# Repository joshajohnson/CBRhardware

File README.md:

# Canberra Hardware Meetup
A monthly hardware meetup for anyone interested in electronics / hardware. 

Held on the second Monday of each month, 6-8pm, at [Infosect](https://www.infosectcbr.com.au), 2/9 Beaconsfield Street, Fyshwick, 2609 ACT.  

We'll cover topics such as PCB design / layout, embedded programming, tips and tricks to make hardware less hard, and everything in between.   

All skill levels welcome, and feel free to bring along any projects you are working on or need a hand with as well.  

If you have any suggestions about topics to discuss / changes to make, please get in touch.

## 11/11/19 - Test and Measurement
An unprepared talk on the wonderful world which is electronic test and measurement, discussing common tools, how they work, pitfalls, where to cheap out, and Josh's unsuccessful attempt at designing a VNA.

### Future Events 

|Date|Topic|
|-|-|
|11/11/19|Test and Measurement|

### Past Events

|Date|Topic|
|-|-|
|8/4/19|Intro to KiCad / How to design a PCB|
|13/5/19|uC101: Intro to Microcontrollers / How to interface to the real world|
|10/6/19|Breadboard to PC Board|
|8/7/19|uC102: Embedded Communication Protocols / ADC|
|12/8/19|Further PCB Design / Manufacturing / KiCad|
|9/9/19|WTFpga Workshop|
|28/10/19|More FPGA!|

## 8/4/19 - Intro to KiCad / How to design a PCB

A workshop going over how to design a printed circuit board in KiCad.  

Aimed at beginners who haven't designed many boards before, or folks who have design experience but haven't used KiCad much.  

Feel free to bring a laptop with [KiCad 5.1](http://kicad-pcb.org/download/) installed if you want to design along, otherwise just come along and ask questions as we go. I would highly suggest bringing a mouse as well, as layout with a trackpad is not much fun. 

The [SAO101](/SAO101) folder contains resources which will be used on the night.

## 13/5/19 - uC101: Intro to Microcontrollers / How to interface with the real world

A workshop delving into the low level details of how you can use a microcontroller to interface with the physical world.   

Will be going below the Arduino abstraction layer to directly interface with registers and peripherals on an ATmega328p, allowing us to interact with switches, rotary encoders, and LEDs.   

You'll learn why buttons don't turn on just once when you press them and ways to get around this issue, along with how custom silicon on the chip can take the workload off your processor. 

If time allows will also cover communication protocols and ADCs, however that will most likely be a different months topic. 

Please bring along a laptop with the [Arduino IDE](https://www.arduino.cc/en/main/software) installed, along with a Mini-USB cable to connect to the microcontroller with. 
Josh will have the installer files and spare USB cables on the night, but will not be enough for everyone. 
The [uC101](/uC101) folder contains resources which will be used.

## 10/6/19 - Breadboard to PC Board

Prototyped a circuit on a breadboard, and want to get it onto a printed cicruit board but not sure how? If so this talk is for you!  
We will be going over how to to take a bunch of breakout boards with wires flying between them and get it onto a professional looking PCB.  
Multiple common microcontrollers, breakout boards, and other handy components will be covered, allowing you to take your electronic design to the next level. 

## 8/7/19 - uC102: Embedded Communication Protocols / ADC

Following on from uC101 in which the low level functions of a microcontroller were explored, this workshop will delve into how embedded devices communicate, along with touching on Analog to Digital Converters. 

UART, SPI, I2C, and JTAG will all be discussed, along with writing code and communicating with UART, SPI, and I2C devices.

Please bring along a laptop with the [Arduino IDE](https://www.arduino.cc/en/main/software) installed. 
Josh will have the installer files on the night as well. 
The [uC102](/uC102) folder contains resources which will be used.

## 12/7 8/19 - furtherPCB: PCB Design / Manufacturing / KiCad

A workshop delving into more detail about PCB design, including 4+ layer stack ups, impedance controlled traces and boards, layout tips, and looking at what the modern state of the art is in PCB manufacturing and assembly.

We will also discuss tools and how to use them to achieve the above mentioned design considerations, followed by looking at some of Josh's projects and identifying where these techniques have been utilised.

## 9/9/19 - WTFpga Workshop

2 hour crash course in FPGAs and Verilog.

Unlike most meetups where all you need to do is show up, this workshop will require software to be installed in advance and hardware to be acquired.

Have a read of the [WTFpga Readme](WTFpga/README.md) and let Josh know if there are any questions.

## 28/10/19 Topic: FPGA Workshop, continued. 
Following on from the WTFpga workshop, we will discuss some of the key details about FPGA function, programming, debugging, and hopefully explain some of the questions which arose at the previous workshop.

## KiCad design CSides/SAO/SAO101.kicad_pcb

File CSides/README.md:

# Electronic Hardware Design

This talk will cover the process of designing, manufacturing, and assembling electronic hardware, with a focus on how to use KiCad to design and layout a PCB. 
Using a keyboard Josh designed as an example, aspects of the process such as circuit design, PCB layout and assembly, along with programming and mechanical design will be demonstrated, with the goal of providing an overview of the process for anyone interested in designing their own hardware.

**Josh Johnson**

Josh is passionate about electronic design and spends far too much time designing boards and writing firmware. 
He is currently in his final semester of university, and is looking forward to joining the real world next year with a product development role in automotive. 

### Keyboard Design Files
Design files for the keyboard discussed can be found [here](https://github.com/joshajohnson/MacroKeyboard).  
If you are considering assembling the above board, modifying it for your own use, or designing one from scratch, feel free to get in touch as there are some things I would change on that board for a new revision. 

### SAO Design
The `SAO` folder has a partial KiCad project with everything you need to make a SAO for BSides 2020.
The schematic is known good, so all you need to do is make an awesome design and ensure is passes DRC.
A completed design is [also available](https://github.com/joshajohnson/CBRhardware/tree/master/SAO101), along with Josh's 2019 [WarGames SAO](https://github.com/joshajohnson/WarGames_SAO).
### Questions? 
Feel free to get in touch with any questions.  
No guarantees I'll be able to help, but will try my best! 

Email: `josh at joshajohnson dot com`  
Twitter: `@_joshajohnson`  
BSidesCbr Slack: `josh`

### Resources:   
[PCB Design in Reverse](https://www.youtube.com/watch?v=CV68US8gZMk)  
[PCB Design Tutorial PDF](https://alternatezone.com/electronics/files/PCBDesignTutorialRevA.pdf)  
[Chris Gammell / Contextual Electronics](https://www.youtube.com/user/contextualelectronic/videos)  
[Digikey KiCad Series](https://www.youtube.com/watch?v=vaCVh2SAZY4)  
[Lintek Process Capabilities](http://www.lintek.com.au/wordpress/wp-content/uploads/Design-Capabilities-v2.7.pdf)
[Robert Feranec - Layout Videos](https://www.youtube.com/user/matarofe/videos)  
[100 Hardware Design Tips](https://www.youtube.com/watch?v=ZpMvKJzZk90&list=PLXvLToQzgzddPKq_txEXNe0pxaSHqPtMO)    
[Review of PCB Layout](https://www.youtube.com/watch?v=HZVod5AFrVI)  
[PCB Art](http://www.andrewsowa.com/blog/2017/3/19/creating-the-benchoff-nickel)  
[How I make Shitty Add-ons](https://www.youtube.com/watch?v=61NFK9KW_4s)  
[Interactive BOM](https://github.com/openscopeproject/InteractiveHtmlBom)

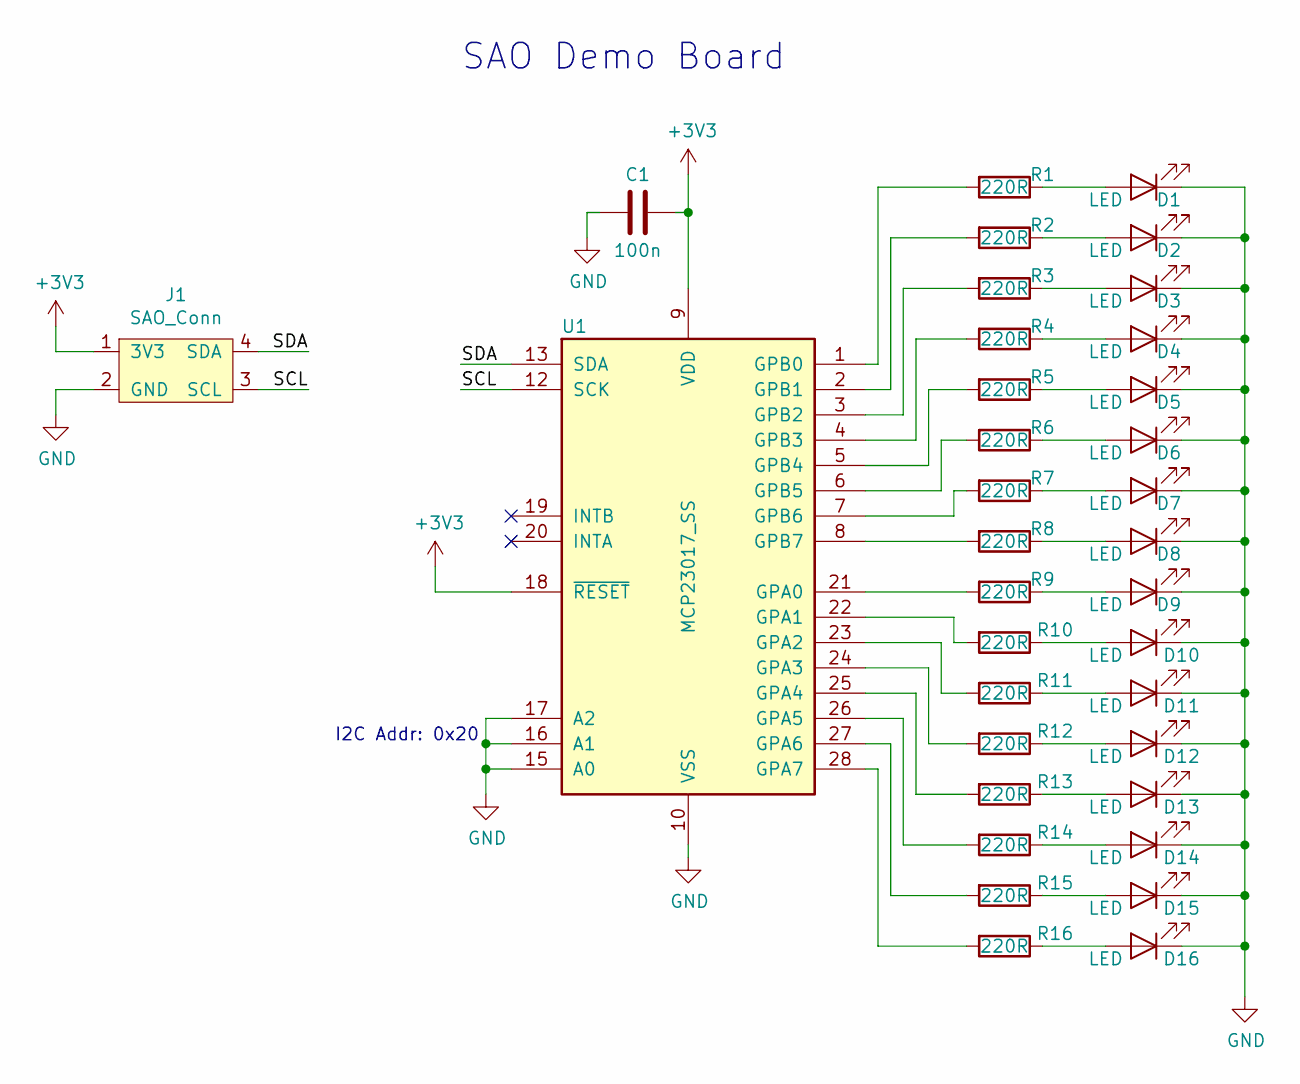
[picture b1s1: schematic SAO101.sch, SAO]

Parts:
C1: 100n; C_0805_2012Metric
D1, D2, D3, D4, D5, D6, D7, D8, D9, D10, D11, D12, D13, D14, D15, D16: LED; LED_1206_3216Metric_Pad1.42x1.75mm_HandSolder
J1: SAO_Conn; SAO
R1, R2, R3, R4, R5, R6, R7, R8, R9, R10, R11, R12, R13, R14, R15, R16: 220R; R_1206_3216Metric_Pad1.42x1.75mm_HandSolder
U1: MCP23017_SS; SSOP-28_5.3x10.2mm_P0.65mm

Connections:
+3V3: C1.1, J1.1 (3V3), U1.9 (VDD), U1.18 (~RESET~)
/SCL: J1.3 (SCL), U1.12 (SCK)
/SDA: J1.4 (SDA), U1.13 (SDA)
GND: C1.2, D1.1 (K), D2.1 (K), D3.1 (K), D4.1 (K), D5.1 (K), D6.1 (K), D7.1 (K), D8.1 (K), D9.1 (K), D10.1 (K), D11.1 (K), D12.1 (K), D13.1 (K), D14.1 (K), D15.1 (K), D16.1 (K), J1.2 (GND), U1.10 (VSS), U1.15 (A0), U1.16 (A1), U1.17 (A2)
unnamed: D1.2 (A), R1.1
unnamed: D2.2 (A), R2.1
unnamed: D3.2 (A), R3.1
unnamed: D4.2 (A), R4.1
unnamed: D5.2 (A), R5.1
unnamed: D6.2 (A), R6.1
unnamed: D7.2 (A), R7.1
unnamed: D8.2 (A), R8.1
unnamed: D9.2 (A), R9.1
unnamed: D10.2 (A), R10.1
unnamed: D11.2 (A), R11.1
unnamed: D12.2 (A), R12.1
unnamed: D13.2 (A), R13.1
unnamed: D14.2 (A), R14.1
unnamed: D15.2 (A), R15.1
unnamed: D16.2 (A), R16.1
unnamed: R1.2, U1.1 (GPB0)
unnamed: R2.2, U1.2 (GPB1)
unnamed: R3.2, U1.3 (GPB2)
unnamed: R4.2, U1.4 (GPB3)
unnamed: R5.2, U1.5 (GPB4)
unnamed: R6.2, U1.6 (GPB5)
unnamed: R7.2, U1.7 (GPB6)
unnamed: R8.2, U1.8 (GPB7)
unnamed: R9.2, U1.21 (GPA0)
unnamed: R10.2, U1.22 (GPA1)
unnamed: R11.2, U1.23 (GPA2)
unnamed: R12.2, U1.24 (GPA3)
unnamed: R13.2, U1.25 (GPA4)
unnamed: R14.2, U1.26 (GPA5)
unnamed: R15.2, U1.27 (GPA6)
unnamed: R16.2, U1.28 (GPA7)

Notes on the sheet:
SAO Demo Board
I2C Addr: 0x20

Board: 2 copper layers, 35 parts (0 on the bottom side), 36 nets, no tracks yet.

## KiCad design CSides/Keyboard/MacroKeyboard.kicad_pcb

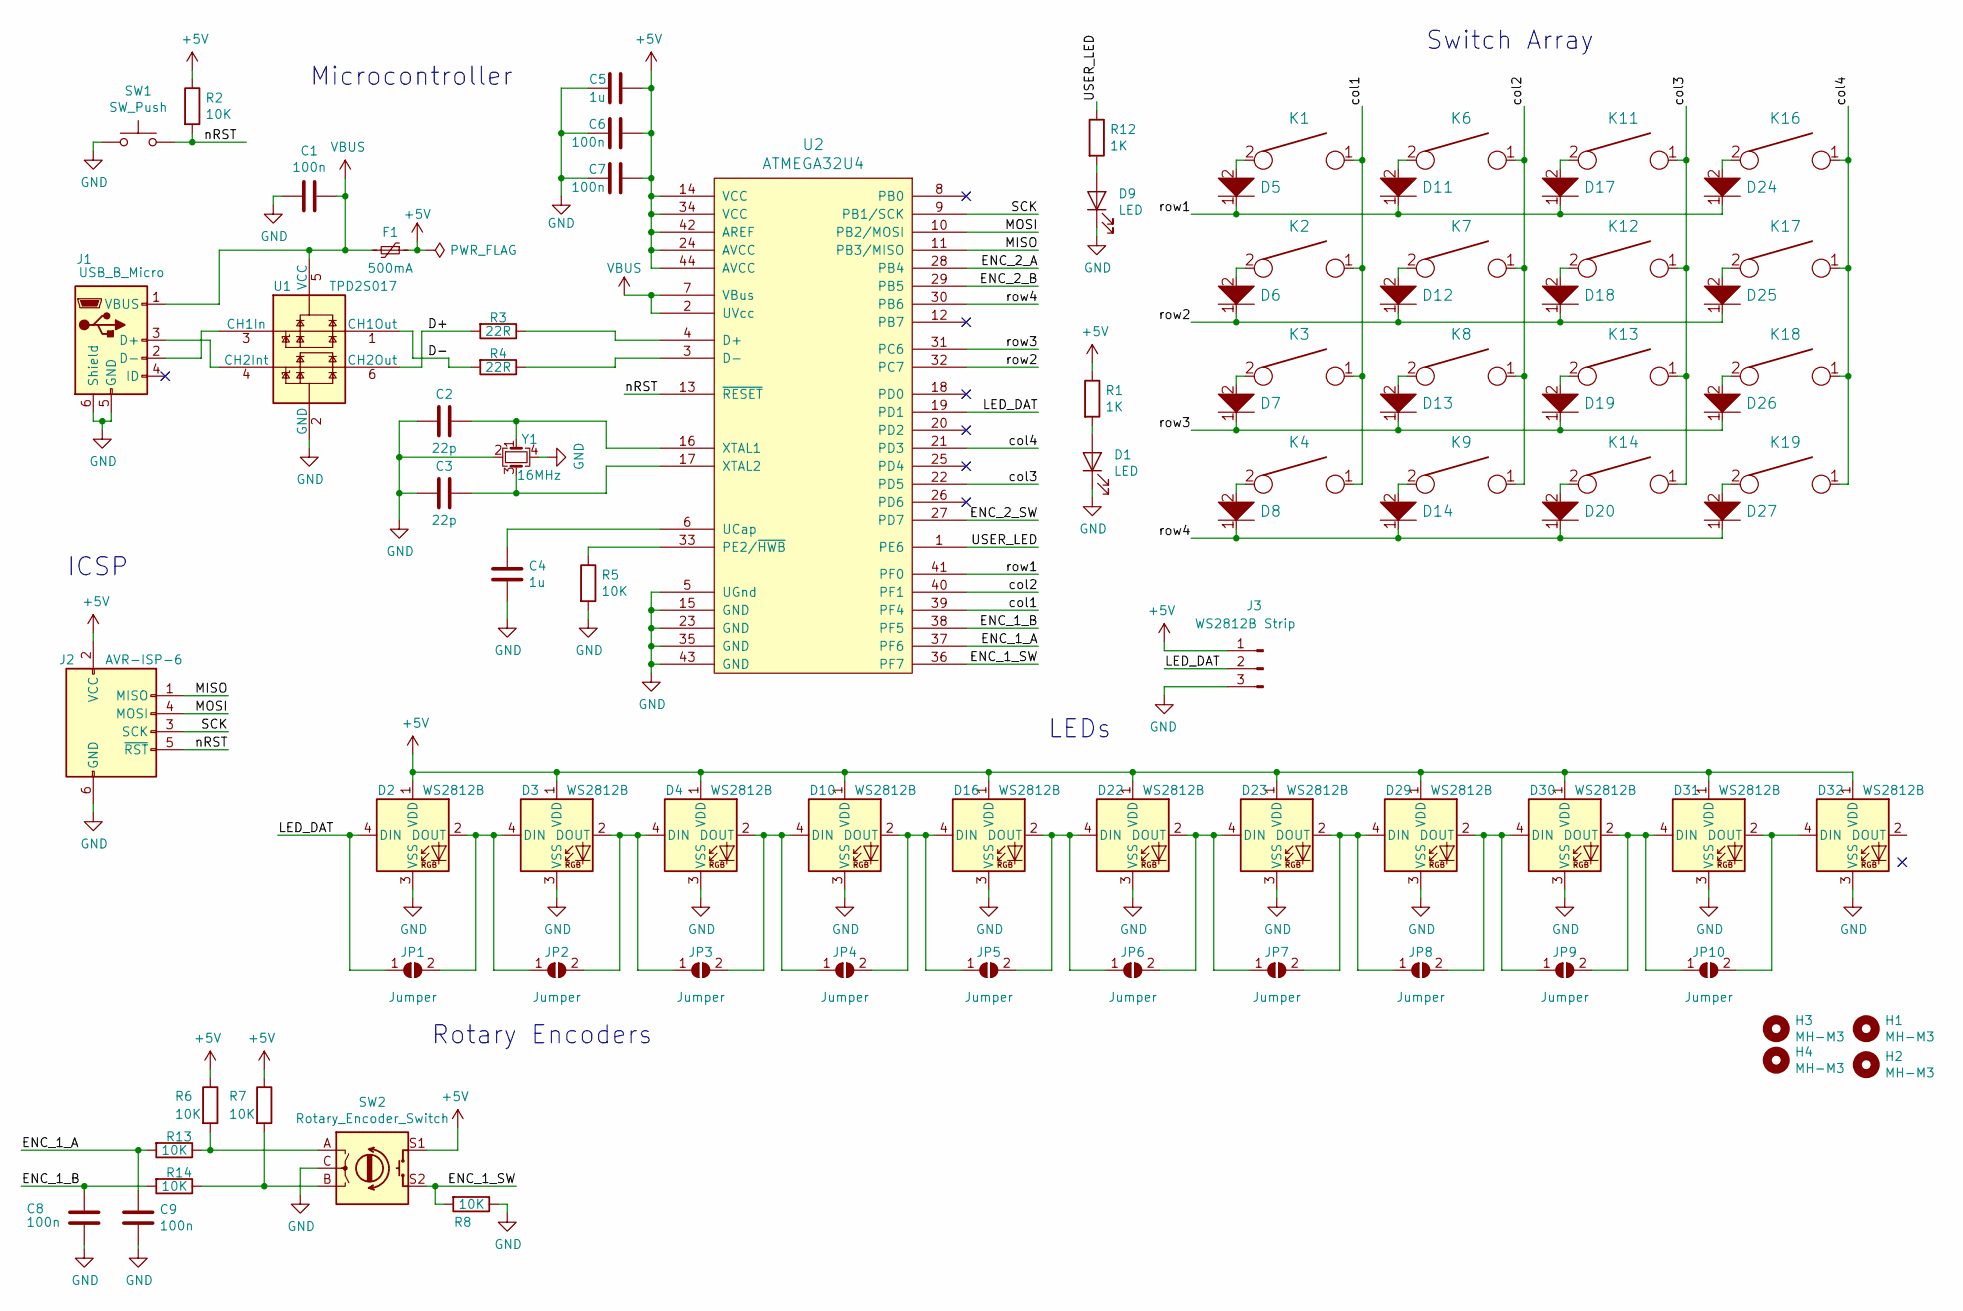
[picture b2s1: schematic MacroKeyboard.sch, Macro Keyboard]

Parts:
C1, C6, C7, C8, C9: 100n; C_0603_1608Metric
C2, C3: 22p; C_0603_1608Metric
C4, C5: 1u; C_0603_1608Metric
D1, D9: LED; LED_0603_1608Metric
D2, D3, D4, D10, D16, D22, D23, D29, D30, D31, D32: WS2812B; LED_WS2812B_PLCC4_5.0x5.0mm_P3.2mm
D5, D6, D7, D8, D11, D12, D13, D14, D17, D18, D19, D20, D24, D25, D26, D27: D; D_SOD-323
F1: 500mA; Fuse_0805_2012Metric
H1, H2, H3, H4: MH-M3; MountingHole_3.2mm_M3_ISO14580
J1: USB_B_Micro; MicroUSB_Aliexpress
J2: AVR-ISP-6; AVR_Programmer_SMD
J3: WS2812B Strip; PinPad_1x03_P2.54mm
JP1, JP2, JP3, JP4, JP5, JP6, JP7, JP8, JP9, JP10: Jumper; SolderJumper-2_P1.3mm_Open_RoundedPad1.0x1.5mm
K1, K2, K3, K4, K6, K7, K8, K9, K11, K12, K13, K14, K16, K17, K18, K19: KEYSW; SW_Cherry_MX1A_1.00u_PCB
R1, R12: 1K; R_0603_1608Metric
R2, R5, R6, R7, R8, R13, R14: 10K; R_0603_1608Metric
R3, R4: 22R; R_0603_1608Metric
SW1: SW_Push; Small_Tact_Switch
SW2: Rotary_Encoder_Switch; RotaryEncoder_Alps_EC11E-Switch_Vertical_H20mm_CircularMoun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
U1: TPD2S017; SOT-23-6
U2: ATMEGA32U4; TQFP-44_10x10mm_P0.8mm
Y1: 16MHz; Crystal_SMD_3225-4Pin_3.2x2.5mm

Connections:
+5V: C5.1, C6.2, C7.2, D2.1 (VDD), D3.1 (VDD), D4.1 (VDD), D10.1 (VDD), D16.1 (VDD), D22.1 (VDD), D23.1 (VDD), D29.1 (VDD), D30.1 (VDD), D31.1 (VDD), D32.1 (VDD), F1.1, J2.2 (VCC), J3.1, R1.1, R2.1, R6.1, R7.1, SW2.S1, U2.14 (VCC), U2.24 (AVCC), U2.34 (VCC), U2.42 (AREF), U2.44 (AVCC)
/D+: R3.2, U1.6 (CH2Out)
/D-: R4.2, U1.1 (CH1Out)
/ENC_1_A: C9.1, R13.2, U2.37 (PF6)
/ENC_1_B: C8.1, R14.2, U2.38 (PF5)
/ENC_1_SW: R8.2, SW2.S2, U2.36 (PF7)
/LED_DAT: D2.4 (DIN), J3.2, JP1.1 (A), U2.19 (PD1)
/MISO: J2.1 (MISO), U2.11 (PB3/MISO)
/MOSI: J2.4 (MOSI), U2.10 (PB2/MOSI)
/SCK: J2.3 (SCK), U2.9 (PB1/SCK)
/USER_LED: R12.1, U2.1 (PE6)
/col1: K1.1, K2.1, K3.1, K4.1, U2.39 (PF4)
/col2: K6.1, K7.1, K8.1, K9.1, U2.40 (PF1)
/col3: K11.1, K12.1, K13.1, K14.1, U2.22 (PD5)
/col4: K16.1, K17.1, K18.1, K19.1, U2.21 (PD3)
/nRST: J2.5 (~RST), R2.2, SW1.2, U2.13 (~RESET)
/row1: D5.1, D11.1, D17.1, D24.1, U2.41 (PF0)
/row2: D6.1, D12.1, D18.1, D25.1, U2.32 (PC7)
/row3: D7.1, D13.1, D19.1, D26.1, U2.31 (PC6)
/row4: D8.1, D14.1, D20.1, D27.1, U2.30 (PB6)
GND: C1.2, C2.2, C3.2, C4.2, C5.2, C6.1, C7.1, C8.2, C9.2, D1.1 (K), D2.3 (VSS), D3.3 (VSS), D4.3 (VSS), D9.1 (K), D10.3 (VSS), D16.3 (VSS), D22.3 (VSS), D23.3 (VSS), D29.3 (VSS), D30.3 (VSS), D31.3 (VSS), D32.3 (VSS), J1.5 (GND), J1.6 (Shield), J2.6 (GND), J3.3, R5.2, R8.1, SW1.1, SW2.C, U1.2 (GND), U2.5 (UGnd), U2.15 (GND), U2.23 (GND), U2.35 (GND), U2.43 (GND), Y1.2, Y1.4
unnamed: C2.1, U2.16 (XTAL1), Y1.1
unnamed: C3.1, U2.17 (XTAL2), Y1.3
unnamed: C4.1, U2.6 (UCap)
unnamed: D1.2 (A), R1.2
unnamed: D2.2 (DOUT), D3.4 (DIN), JP1.2 (B), JP2.1 (A)
unnamed: D3.2 (DOUT), D4.4 (DIN), JP2.2 (B), JP3.1 (A)
unnamed: D5.2, K1.2
unnamed: D6.2, K2.2
unnamed: D7.2, K3.2
unnamed: D8.2, K4.2
unnamed: D9.2 (A), R12.2
unnamed: D10.2 (DOUT), D16.4 (DIN), JP4.2 (B), JP5.1 (A)
unnamed: D4.2 (DOUT), D10.4 (DIN), JP3.2 (B), JP4.1 (A)
unnamed: D11.2, K6.2
unnamed: D12.2, K7.2
unnamed: D13.2, K8.2
unnamed: D14.2, K9.2
unnamed: D16.2 (DOUT), D22.4 (DIN), JP5.2 (B), JP6.1 (A)
unnamed: D17.2, K11.2
unnamed: D18.2, K12.2
unnamed: D19.2, K13.2
unnamed: D20.2, K14.2
unnamed: D22.2 (DOUT), D23.4 (DIN), JP6.2 (B), JP7.1 (A)
unnamed: D23.2 (DOUT), D29.4 (DIN), JP7.2 (B), JP8.1 (A)
unnamed: D24.2, K16.2
unnamed: D25.2, K17.2
unnamed: D26.2, K18.2
unnamed: D27.2, K19.2
unnamed: D29.2 (DOUT), D30.4 (DIN), JP8.2 (B), JP9.1 (A)
unnamed: D30.2 (DOUT), D31.4 (DIN), JP9.2 (B), JP10.1 (A)
unnamed: D31.2 (DOUT), D32.4 (DIN), JP10.2 (B)
unnamed: J1.2 (D-), U1.3 (CH1In)
unnamed: J1.3 (D+), U1.4 (CH2Int)
unnamed: R3.1, U2.4 (D+)
unnamed: R4.1, U2.3 (D-)
unnamed: R5.1, U2.33 (PE2/~HWB)
unnamed: R6.2, R13.1, SW2.A
unnamed: R7.2, R14.1, SW2.B
VBUS: C1.1, F1.2, J1.1 (VBUS), U1.5 (VCC), U2.2 (UVcc), U2.7 (VBus)

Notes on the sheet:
Switch Array
LEDs
ICSP
Microcontroller
Rotary Encoders

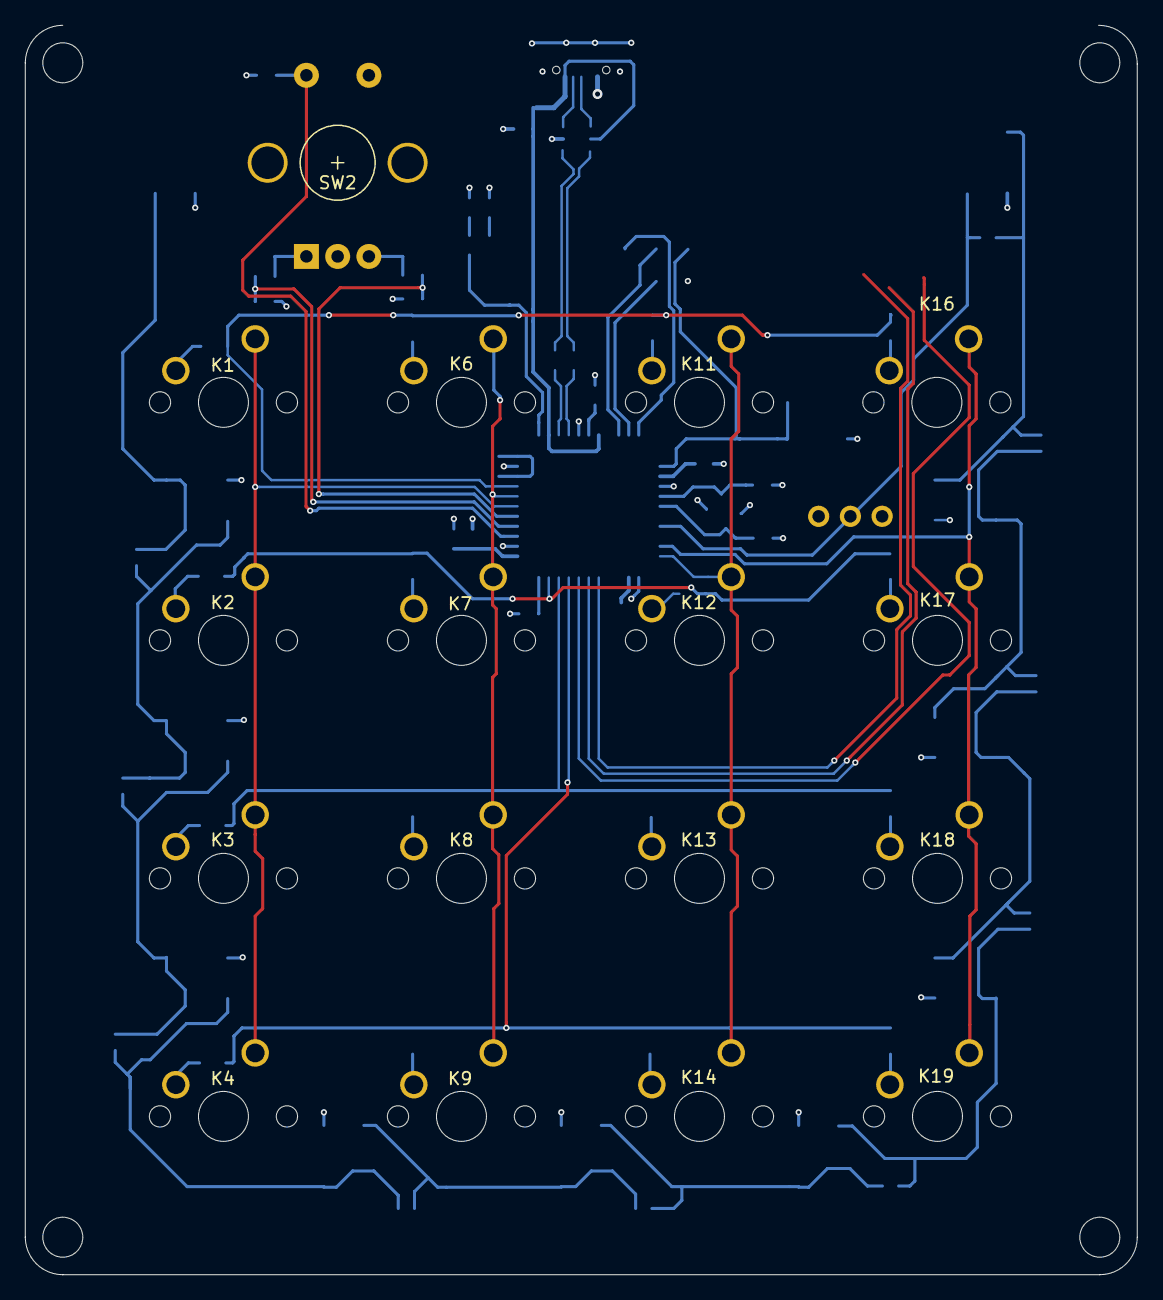
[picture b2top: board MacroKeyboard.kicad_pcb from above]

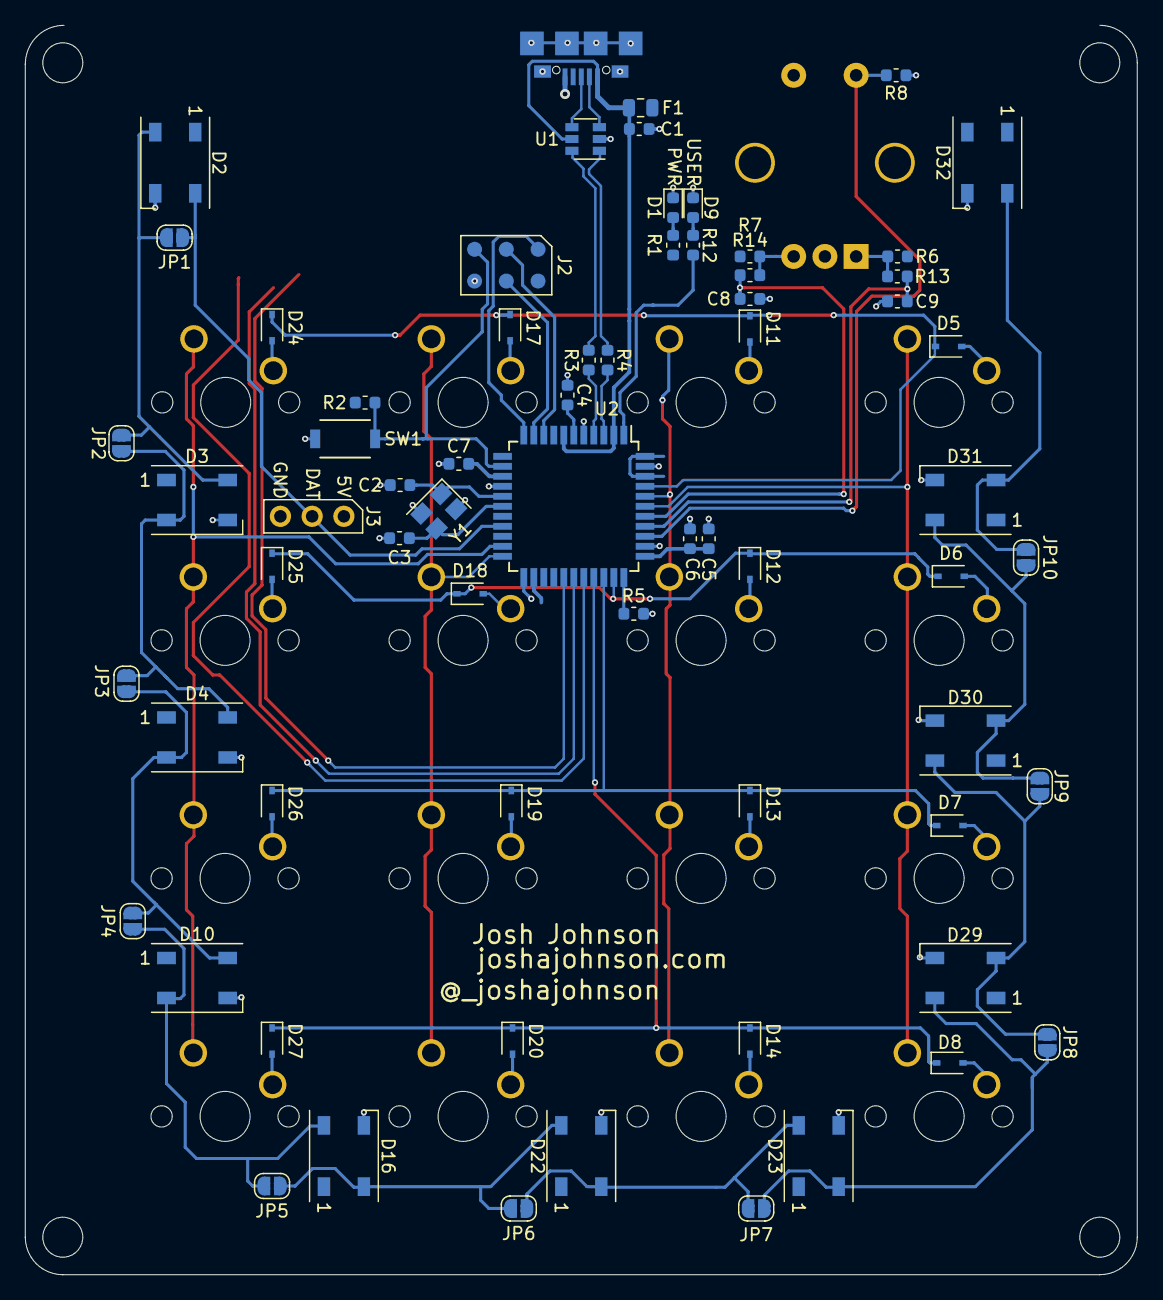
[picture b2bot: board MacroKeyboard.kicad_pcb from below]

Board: 2 copper layers, 89.0 x 100.0 mm, 88 parts (67 on the bottom side), 60 nets.

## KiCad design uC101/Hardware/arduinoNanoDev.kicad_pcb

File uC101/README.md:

# uC101
Project files for an intro to microcontrollers workshop.  

### To get up and running:
Install Arduino IDE  
Copy the uC101Library folder to `/Arduino/libraries`  
In Arduino IDE:  
`File->Examples->uC101->blink`  
`Tools->Board->Arduino Nano`  
`Tools->Processor->ATmega328p` or `Tools->Processor->ATmega328p (Old Bootloader)`  
`Tools->Port->$comPort`

Run `blink.ino` and confirm that the onboard LED is blinking

### Resources:   

[Embedded FM Podcast](embedded.fm) Look through old episodes for fundamentals  
[Making Embedded Systems](http://shop.oreilly.com/product/0636920017776.do) Josh has a copy you can borrow  
[Google 'problem' + avr](http://lmgtfy.com/?q=problem+avr)  
[Adafruit](https://www.adafruit.com/) [Sparkfun](https://www.sparkfun.com/) HW and SW resources  

#### Alternative Platforms
[PlatformIO](https://platformio.org/) Highly recomended replacement for Arduino IDE  
[STM32 System Workbench](http://www.openstm32.org/System%2BWorkbench%2Bfor%2BSTM32) Open source STM32 IDE / toolchain  

### Troubleshooting:

#### Windows
If after installing the Arduino software, you are missing a virtual COM port to communicate with your board, and the Device Manager is missing the usb2.0-serial driver, install the below driver:

http://www.wch.cn/download/CH341SER_ZIP.html

This is due to a CH340G USB to serial chip being used on the Arduino Nano.

(Thanks Wayne for the above fix!)

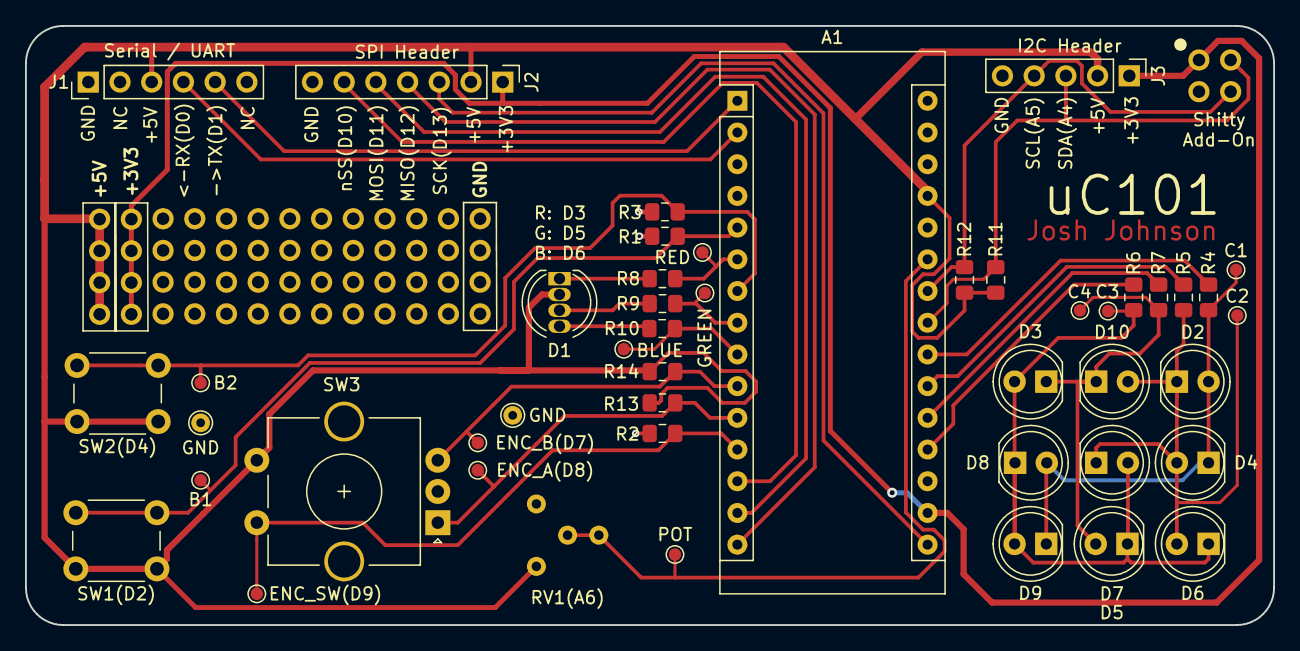
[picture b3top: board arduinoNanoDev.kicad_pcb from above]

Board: 2 copper layers, 100.0 x 48.0 mm, 55 parts (0 on the bottom side), 31 nets.

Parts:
A1: Arduino_Nano_v3.x; Arduino_Nano
D1: LED_RAGB; LED_D5.0mm-4_RGB
D2, D3, D4, D5, D6, D7, D8, D9, D10: LED; LED_D5.0mm
J1: Serial / UART; PinHeader_1x06_P2.54mm_Vertical
J2: SPI Header; PinHeader_1x07_P2.54mm_Vertical
J3: I2C Header; PinHeader_1x05_P2.54mm_Vertical
J4: SAO_Conn; SAO
J5, J6, J7, J8: Conn_01x10; PinHole_1x10_P2.54mm_Vertical
J9, J10, J11: Conn_01x04; PinHole_1x04_P2.54mm_Vertical
R1, R2, R3, R13, R14: 10K; R_0805_2012Metric_Pad1.15x1.40mm_HandSolder
R4, R5, R6, R7, R8, R9, R10: 330R; R_0805_2012Metric_Pad1.15x1.40mm_HandSolder
R11, R12: 4K7; R_0805_2012Metric_Pad1.15x1.40mm_HandSolder
RV1(A6): 10K Pot; PotentiometerAliExpress
SW1(D2), SW2(D4): SW_Push; SW_PUSH_6mm_H4.3mm
SW3: Rotary_Encoder_Switch; RotaryEncoder_Alps_EC11E-Switch_Vertical_H20mm_CircularMoun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
TP1: ENC_B(D7); TestPoint_Pad_D1.0mm
TP2: B1; TestPoint_Pad_D1.0mm
TP3: ENC_A(D8); TestPoint_Pad_D1.0mm
TP4: B2; TestPoint_Pad_D1.0mm
TP5: C1; TestPoint_Pad_D1.0mm
TP6: C2; TestPoint_Pad_D1.0mm
TP7: C3; TestPoint_Pad_D1.0mm
TP8: C4; TestPoint_Pad_D1.0mm
TP9: RED; TestPoint_Pad_D1.0mm
TP10: BLUE; TestPoint_Pad_D1.0mm
TP11: GREEN; TestPoint_Pad_D1.0mm
TP12: POT; TestPoint_Pad_D1.0mm
TP13, TP14: GND; TestPoint_THTPad_D1.5mm_Drill0.7mm
TP15: ENC_SW(D9); TestPoint_Pad_D1.0mm

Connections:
+3V3: A1.17, J2.1, J3.1, J4.1, J11.1, J11.2, J11.3, J11.4
+5V: A1.27, D1.2, J1.3, J2.2, J3.2, J10.1, J10.2, J10.3, J10.4, R11.1, R12.1, R13.1, R14.1, RV1(A6).3, SW1(D2).1, SW2(D4).1, SW3.S1
/BUTTON_1: A1.5, R1.1, SW1(D2).2, TP2.1
/BUTTON_2: A1.7, R3.1, SW2(D4).2, TP4.1
/CHARILE_1: A1.22, R4.2
/CHARILE_2: A1.21, R5.2
/CHARILE_3: A1.19, R6.2
/CHARILE_4: A1.20, R7.2
/ENCODER_A: A1.11, R13.2, SW3.A, TP3.1
/ENCODER_B: A1.10, R14.2, SW3.B, TP1.1
/ENCODER_SW: A1.12, R2.1, SW3.S2, TP15.1
/LED_BLUE: A1.9, R10.1, TP10.1
/LED_GREEN: A1.8, R9.1, TP11.1
/LED_RED: A1.6, R8.1, TP9.1
/MISO: A1.15, J2.4
/MOSI: A1.14, J2.5
/POT: A1.25, RV1(A6).2, TP12.1
/RX: A1.2, J1.4
/SCK: A1.16, J2.3
/SCL: A1.24, J3.4, J4.3, R12.2
/SDA: A1.23, J3.3, J4.4, R11.2
/TX: A1.1, J1.5
/nSS: A1.13, J2.6
GND: A1.4, A1.29, J1.1, J2.7, J3.5, J4.2, J9.1, J9.2, J9.3, J9.4, R1.2, R2.2, R3.2, RV1(A6).1, SW3.C, TP13.1, TP14.1
unnamed: D1.1, R8.2
unnamed: D1.3, R9.2
unnamed: D1.4, R10.2
unnamed: D2.2, D4.1, D8.2, D9.1, R4.1, TP5.1
unnamed: D3.2, D5.1, D6.1, D7.2, D8.1, D9.2, R6.1, TP7.1
unnamed: D3.1, D5.2, D10.1, R7.1, TP8.1
unnamed: D2.1, D4.2, D6.2, D7.1, D10.2, R5.1, TP6.1

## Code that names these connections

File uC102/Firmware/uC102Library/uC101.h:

#ifndef __UC101_H__
#define __UC101_H__

#include <stdint.h>

// uC101 Pin Definitions
#define BUTTON_1 	PD2
#define BUTTON_2 	PD4

#define ENCODER_SW 	PB1
#define ENCODER_A 	PB0
#define ENCODER_B 	PD7

#define LED_RED 	PD3
#define LED_GREEN 	PD5
#define LED_BLUE 	PD6

#define CHARLIE_1 	PC3
#define CHARLIE_2 	PC2
#define CHARLIE_3 	PC0
#define CHARLIE_4 	PC1

#define UART_RX 	PD0
#define UART_TX 	PD1

#define SPI_MOSI 	PB3
#define SPI_MISO    PB4
#define SPI_SCK     PB5
#define SPI_nSS     PB2

#define I2C_SDA 	PC4
#define I2C_SCL     PC5

#define POT 		ADC6

// Port Definitions
#define BUTTON_1_PORT 	PORTD
#define BUTTON_2_PORT 	PORTD

#define ENCODER_SW_PORT PORTB
#define ENCODER_A_PORT 	PORTB
#define ENCODER_B_PORT 	PORTD

#define LED_RED_PORT 	PORTD
#define LED_GREEN_PORT 	PORTD
#define LED_BLUE_PORT 	PORTD

#define CHARLIE_1_PORT 	PORTC
#define CHARLIE_2_PORT 	PORTC
#define CHARLIE_3_PORT 	PORTC
#define CHARLIE_4_PORT 	PORTC

#define UART_RX_PORT 	PORTD
#define UART_TX_PORT 	PORTD

#define SPI_MOSI_PORT 	PORTB
#define SPI_MISO_PORT 	PORTB
#define SPI_SCK_PORT 	PORTB
#define SPI_nSS_PORT 	PORTB

#define I2C_SDA_PORT	PORTC
#define I2C_SCL_PORT	PORTC

//  Pin/Port Manipulation Macros
#define clearBit(port,pin) 	(port) &= ~(1<<(pin))
#define setBit(port,pin) 	(port) |= (1<<(pin))
#define toggleBit(port,pin) (port) ^= (1<<(pin))

#define ledOn(pin) 			(PORTD) &= ~(1<<(pin))
#define ledOff(pin) 		(PORTD) |= (1<<(pin))
#define ledToggle(pin) 		(PORTD) ^= (1<<(pin))

#define dirOut(port,pin) 	(*(&port-1)) |= (1<<(pin))
#define dirIn(port,pin) 	(*(&port-1)) &= ~(1<<(pin))

#define readPin(port,pin) 	(((*(&port-2)) & (1<<pin)) ? 1 : 0)

#endif

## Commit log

2019-03-22 Added README and SAO101 folder
2019-03-22 fix typos and layout
2019-03-23 one day I'll learn to spell + updated render
2019-03-23 added more resources
2019-03-25 First draft of SAO101 slides
2019-03-25 Updated presentation
2019-04-03 Updated slides
2019-04-04 Changed resources in readme
2019-04-04 update schematic with I2C address
2019-04-06 uC101 Schematic and 3d models complete
2019-04-06 Prelim route of uC101 board
2019-04-07 added more slides and resources, small routing changes
2019-04-07 added test points to uC101 board
2019-04-08 code working + slide updates
2019-04-08 more uC101 board changes
2019-04-09 more changes to arduinoNanoDev board
2019-04-11 More board updates + updated readme
2019-04-13 More board changes + updated RouteMe with latest netlist
2019-04-22 Panellisation and sending off of gerbers
2019-04-22 changed github url and removed bit.ly links
2019-05-02 some firmware + initial slides
2019-05-02 Bit math added to slides, updated readme with install instructions and resources
2019-05-07 prelim slides done
2019-05-09 code and slides done
2019-05-10 comments++ and moved examples to examples folder
2019-05-10 updated install instructions
2019-05-11 updated code
2019-05-11 Revert "updated code"
    This reverts commit 157852c691c68d74a50b4dac440c551331a0c954.
2019-05-11 new machine, new problems
2019-05-11 changed install instructions
2019-05-13 small code and slide changes
2019-05-15 Fix information for getting the USB2.0-serial driver working on Windows.
2019-05-15 linked directly to Ch340G driver
2019-05-21 added breadboard2pcboard/README.md
2019-05-31 fixed library issues with uC101
2019-06-03 bb2pcb WIP slides + added test firmware for uC101 boards
2019-06-04 more slides + added example schematics
2019-06-05 added mechanical photos
2019-06-05 embedded.fm is back to working
2019-06-05 added bga images
2019-06-09 added designs to be discussed on the night
2019-06-09 updated keyboard schematic
2019-06-10 added uC102 as next event
2019-06-22 spi, uart, and slides begun for uc102
2019-06-23 adc code and slides done
2019-07-03 uc102 slides done
2019-07-06 fixing uc102 typos
2019-07-06 another typo in readme
2019-08-08 initial furtherPCB commit, slides WIP
2019-08-08 draft slides done
2019-08-08 added resources
2019-08-09 more resources and added iBOM to slides
2019-08-09 added fpga repo link
2019-08-12 another revision to slides
2019-08-13 added WTFpga workshop
2019-08-24 updated wtfpga submodule
2019-09-13 add csides talk
2019-09-17 update WTFpga
2019-10-01 updated fpga 102 date
2019-10-26 added gateware
2019-10-28 add gen_gamma_table.c
2019-11-05 add test and measurement talk
2019-11-11 updated resources
